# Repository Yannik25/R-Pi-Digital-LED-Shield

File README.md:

# R-Pi-Digital-LED-Shield

Created with KiCad

Main purpose for me was to use this board with my 3D Printer with [OctoPrint](https://octoprint.org) and this add-on: [ws281x-led-status](https://cp2004.gitbook.io/ws281x-led-status/) but will also work with: [rpi_ws281x](https://github.com/jgarff/rpi_ws281x) and similar Software.

## Current status: Designed 
 
## Features
- Power R-Pi through DC Jack or screw terminal (over and reverse voltage Protection)
- Onboard Digital LED
	- can be skipped by bridging the solderpoints at JP1
- Level Shifter from 3.3V to 5V

## The Hardware:

## Contributions

Feel free to open Pull Requests or Issues

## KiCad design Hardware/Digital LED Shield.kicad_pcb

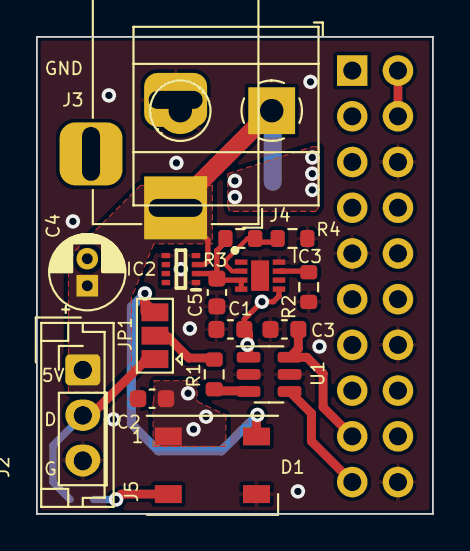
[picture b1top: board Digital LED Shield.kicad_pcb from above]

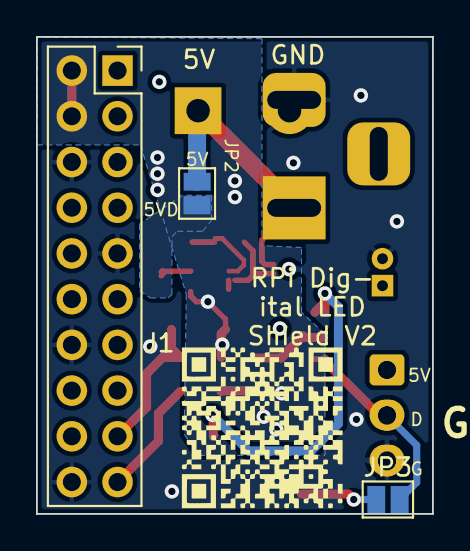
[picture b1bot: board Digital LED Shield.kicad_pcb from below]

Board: 2 copper layers, 22.0 x 26.5 mm, 21 parts (3 on the bottom side), 13 nets.

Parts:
C1, C2, C3, C5: 0.1uF; C_0603_1608Metric
C4: 10uF; CP_Radial_D4.0mm_P1.50mm
D1: WS2812B; LED_WS2812B_PLCC4_5.0x5.0mm_P3.2mm
IC2: LM66200DRLR; SOTFL50P160X60-8N
IC3: TPS259570DSGR; SON50P200X200X80-9N
J1: Conn_02x10_Odd_Even; PinSocket_2x10_P2.54mm_Vertical
J2: Conn_01x03_Male; PinHeader_1x03_P2.54mm_Vertical
J3: Barrel_Jack_MountingPin; BarrelJack_Horizontal
J4: Conn_01x02_Female; TerminalBlock_Phoenix_MKDS-1,5-2-5.08_1x02_P5.08mm_Horizont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
J5: Conn_01x03_Male; JST_EH_B3B-EH-A_1x03_P2.50mm_Vertical
JP1: Jumper_3_Open; SolderJumper-3_P1.3mm_Open_Pad1.0x1.5mm
JP2, JP3: Jumper_2_Open; SolderJumper-2_P1.3mm_Open_Pad1.0x1.5mm
R1: 150; R_0603_1608Metric
R2: 953; R_0603_1608Metric
R3: 1k; R_0603_1608Metric
R4: 296,3k; R_0603_1608Metric
U1: SN74LVC1T45DBV; SOT-23-6

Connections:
+3V3: C3.2, J1.17, U1.6 (VCCB)
+5V: C4.1, IC2.3 (VIN1), J2.1, J3.1, J4.1, J5.1, JP2.1 (A)
+5VL: C5.2, IC2.2 (VOUT_1), IC3.3 (IN_1), IC3.4 (IN_2), R3.1
+5VP: C1.2, C2.1, D1.1 (VDD), IC3.5 (OUT), J1.2, J1.4, JP2.2 (B), U1.1 (VCCA)
/Data: J1.19, U1.4 (B)
DIN: D1.4 (DIN), JP1.3 (B)
DOI: D1.2 (DOUT), JP3.1 (A)
DOUT: J2.2, J5.2, JP1.1 (A), JP3.2 (B)
GND: C1.1, C2.2, C3.1, C4.2, C5.1, D1.3 (VSS), IC2.1 (GND_1), IC2.4 (~ON), IC2.5 (GND_2), IC3.8 (GND_1), IC3.9 (GND_2), J1.6, J1.9, J1.14, J1.20, J2.3, J3.2, J4.2, J5.3, R2.2, R4.2, U1.2 (GND), U1.5 (DIR)
unnamed: IC3.2 (EN/UVLO), R3.2, R4.1
unnamed: IC3.7 (ILM), R2.1
unnamed: JP1.2 (C), R1.1
unnamed: R1.2, U1.3 (A)

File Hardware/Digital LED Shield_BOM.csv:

Comment,Designator,Footprint,LCSC
0.1uF,C1 C2 C3,Capacitor_SMD:C_0603_1608Metric
10uF,C4,Capacitor_THT:CP_Radial_D4.0mm_P1.50mm
WS2812B,D1,LED_SMD:LED_WS2812B_PLCC4_5.0x5.0mm_P3.2mm
LM431BCM3X_NOPB,IC1,LM431BCM3X:SOT95P237X95-3N
LM66200DRLR,IC2,LM66200DRLR:SOTFL50P160X60-8N
150,R1,Resistor_SMD:R_0805_2012Metric
1k,R2,Resistor_SMD:R_0603_1608Metric
10k,R3 R4,Resistor_SMD:R_0603_1608Metric
SN74LVC1T45DBV,U1,Package_TO_SOT_SMD:SOT-23-6

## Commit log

2022-01-14 initial release
2022-01-20 add protection
2022-01-28 Add protection and screw terminal
2022-01-28 Create LICENSE
2022-02-03 Add ordered Version V1
2022-05-09 change lm431 to TPS2420
2022-05-09 update sch and pcb
2022-05-09 update RPI Shield
2022-06-03 add Gerber
2022-11-21 add eFuse for Overvoltage and Overcurrent protection
2023-08-30 Delete Schematic.pdf
    delete old schematic
2023-08-31 update Overvoltage protection resistor value
